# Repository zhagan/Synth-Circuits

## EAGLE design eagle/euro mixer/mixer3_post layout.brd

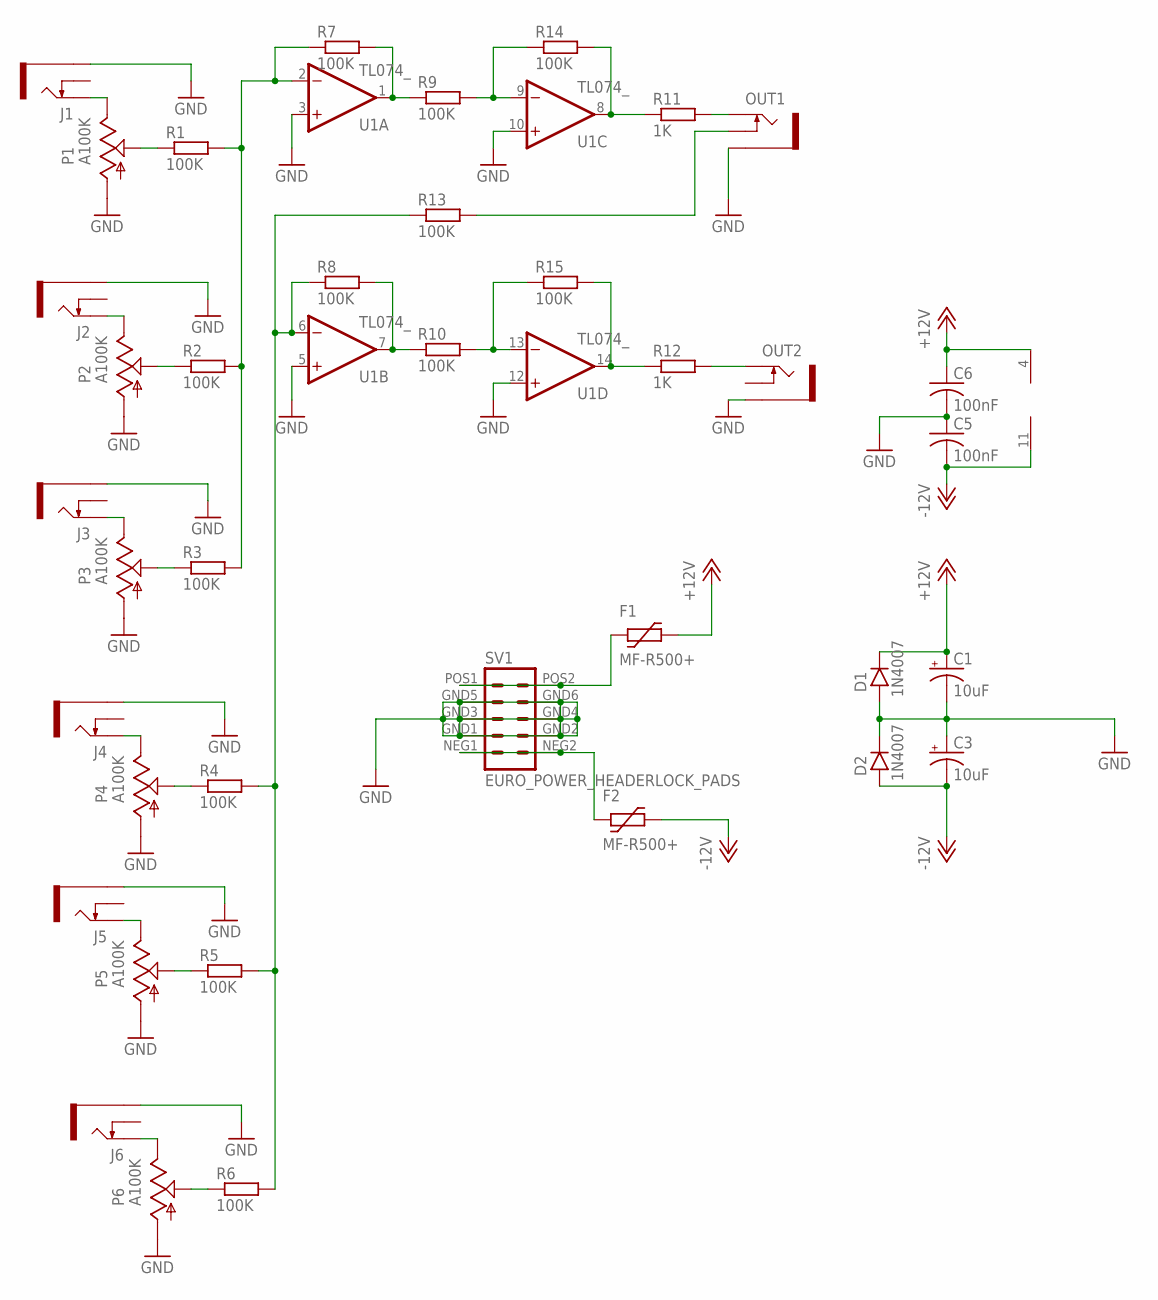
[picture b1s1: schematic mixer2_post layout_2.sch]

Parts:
C1, C3: 10uF; E2,5-7
C5, C6: 100nF; C075-032X103
D1, D2: 1N4007; DO41-3
F1, F2: MF-R500+; BOURNS-MF-R
J1, J2, J3, J4, J5, J6: THONKICONNNEW; WQP-PJ301M-12_JACK
OUT1, OUT2: THONKICONNNEW; WQP-PJ301M-12_JACK
P1, P2, P3, P4, P5, P6: A100K; 9MM_SNAP-IN_POT
R1, R2, R3, R4, R5, R6, R7, R8, R9, R10, R13, R14, R15: 100K; 7MM_RESISTOR
R11, R12: 1K; 7MM_RESISTOR
SV1: EURO_POWER_HEADERLOCK_PADS; EURO_PWR_HEADER_LOCK
U1: TL074_; DIL14

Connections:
+12V: C1.+, C6.1, D1.C, F1.P$2 (2), U1.4 (V+)
-12V: C3.-, C5.2, D2.A, F2.P$2 (2), U1.11 (V-)
GND: C1.-, C3.+, C5.1, C6.2, D1.A, D2.C, J1.P$3_SLEEVE (SLEEVE), J2.P$3_SLEEVE (SLEEVE), J3.P$3_SLEEVE (SLEEVE), J4.P$3_SLEEVE (SLEEVE), J5.P$3_SLEEVE (SLEEVE), J6.P$3_SLEEVE (SLEEVE), OUT1.P$3_SLEEVE (SLEEVE), OUT2.P$3_SLEEVE (SLEEVE), P1.1 (A), P2.1 (A), P3.1 (A), P4.1 (A), P5.1 (A), P6.1 (A), SV1.GND1 (4), SV1.GND2 (3), SV1.GND3 (6), SV1.GND4 (5), SV1.GND5 (8), SV1.GND6 (7), U1.3 (+IN), U1.5 (+IN), U1.10 (+IN), U1.12 (+IN)
unnamed: J2.P$1_TIP (TIP), P2.3 (E)
unnamed: P2.2 (S), R2.1
unnamed: J1.P$1_TIP (TIP), P1.3 (E)
unnamed: P1.2 (S), R1.1
unnamed: J3.P$1_TIP (TIP), P3.3 (E)
unnamed: P3.2 (S), R3.1
unnamed: J4.P$1_TIP (TIP), P4.3 (E)
unnamed: P4.2 (S), R4.1
unnamed: J5.P$1_TIP (TIP), P5.3 (E)
unnamed: P5.2 (S), R5.1
unnamed: J6.P$1_TIP (TIP), P6.3 (E)
unnamed: P6.2 (S), R6.1
unnamed: R1.2, R2.2, R3.2, R7.1, U1.2 (-IN)
unnamed: R8.2, R10.1, U1.7 (OUT)
unnamed: R9.2, R14.1, U1.9 (-IN)
unnamed: OUT1.P$1_TIP (TIP), R11.2
unnamed: R12.1, R15.2, U1.14 (OUT)
unnamed: R10.2, R15.1, U1.13 (-IN)
unnamed: R4.2, R5.2, R6.2, R8.1, R13.1, U1.6 (-IN)
unnamed: R11.1, R14.2, U1.8 (OUT)
unnamed: OUT1.P$2_SWITCH (SWITCH), R13.2
unnamed: OUT2.P$1_TIP (TIP), R12.2
unnamed: R7.2, R9.1, U1.1 (OUT)
unnamed: F2.P$1 (1), SV1.NEG1 (2), SV1.NEG2 (1)
unnamed: F1.P$1 (1), SV1.POS1 (10), SV1.POS2 (9)

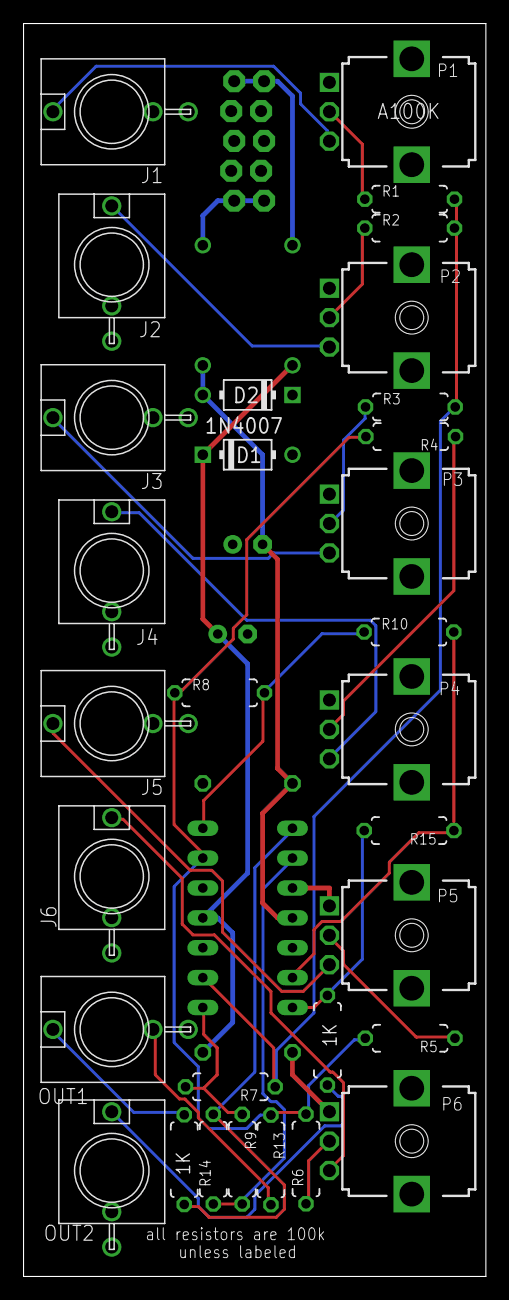
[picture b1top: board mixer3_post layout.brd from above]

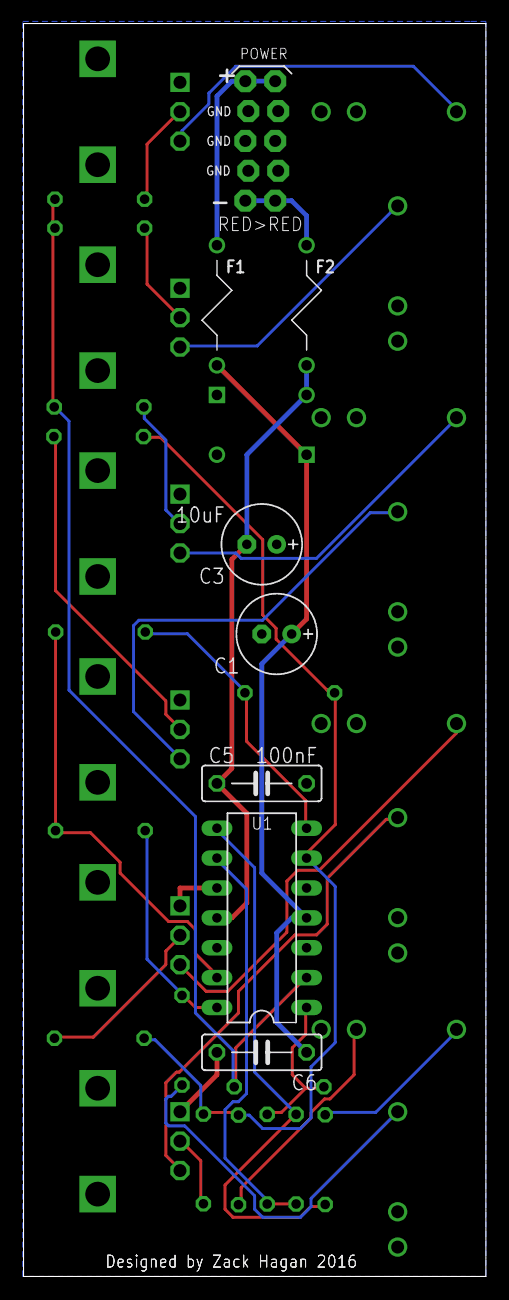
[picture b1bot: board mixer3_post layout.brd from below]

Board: 2 copper layers, 39.3 x 106.5 mm, 39 parts (8 on the bottom side), 28 nets.

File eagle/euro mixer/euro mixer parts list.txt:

Partlist

Exported from mixer3_post layout.sch at 4/12/17 4:11 PM

EAGLE Version 7.3.0 Copyright (c) 1988-2015 CadSoft

Assembly variant: 

Part     Value                      Device                     Package              Library           Sheet

C1       10uF                       CPOL-USE2.5-7              E2,5-7               resistor          1
C3       10uF                       CPOL-USE2.5-7              E2,5-7               resistor          1
C5       100nF                      C-US075-032X103            C075-032X103         resistor          1
C6       100nF                      C-US075-032X103            C075-032X103         resistor          1
D1       1N4007                     1N400X.3                   DO41-3               gm-diodes         1
D2       1N4007                     1N400X.3                   DO41-3               gm-diodes         1
F1       MF-R500+                   MF-R500+                   BOURNS-MF-R          ptc-littlefuse    1
F2       MF-R500+                   MF-R500+                   BOURNS-MF-R          ptc-littlefuse    1
J1       THONKICONNNEW              THONKICONNNEW              WQP-PJ301M-12_JACK   MusicThingModular 1
J2       THONKICONNNEW              THONKICONNNEW              WQP-PJ301M-12_JACK   MusicThingModular 1
J3       THONKICONNNEW              THONKICONNNEW              WQP-PJ301M-12_JACK   MusicThingModular 1
J4       THONKICONNNEW              THONKICONNNEW              WQP-PJ301M-12_JACK   MusicThingModular 1
J5       THONKICONNNEW              THONKICONNNEW              WQP-PJ301M-12_JACK   MusicThingModular 1
J6       THONKICONNNEW              THONKICONNNEW              WQP-PJ301M-12_JACK   MusicThingModular 1
OUT1     THONKICONNNEW              THONKICONNNEW              WQP-PJ301M-12_JACK   MusicThingModular 1
OUT2     THONKICONNNEW              THONKICONNNEW              WQP-PJ301M-12_JACK   MusicThingModular 1
P1       A100K                      9MM_SNAP-IN_POT_           9MM_SNAP-IN_POT      MusicThingModular 1
P2       A100K                      9MM_SNAP-IN_POT_           9MM_SNAP-IN_POT      MusicThingModular 1
P3       A100K                      9MM_SNAP-IN_POT_           9MM_SNAP-IN_POT      MusicThingModular 1
P4       A100K                      9MM_SNAP-IN_POT_           9MM_SNAP-IN_POT      MusicThingModular 1
P5       A100K                      9MM_SNAP-IN_POT_           9MM_SNAP-IN_POT      MusicThingModular 1
P6       A100K                      9MM_SNAP-IN_POT_           9MM_SNAP-IN_POT      MusicThingModular 1
R1       100K                       RESISTOR7MM                7MM_RESISTOR         MusicThingModular 1
R2       100K                       RESISTOR7MM                7MM_RESISTOR         MusicThingModular 1
R3       100K                       RESISTOR7MM                7MM_RESISTOR         MusicThingModular 1
R4       100K                       RESISTOR7MM                7MM_RESISTOR         MusicThingModular 1
R5       100K                       RESISTOR7MM                7MM_RESISTOR         MusicThingModular 1
R6       100K                       RESISTOR7MM                7MM_RESISTOR         MusicThingModular 1
R7       100K                       RESISTOR7MM                7MM_RESISTOR         MusicThingModular 1
R8       100K                       RESISTOR7MM                7MM_RESISTOR         MusicThingModular 1
R9       100K                       RESISTOR7MM                7MM_RESISTOR         MusicThingModular 1
R10      100K                       RESISTOR7MM                7MM_RESISTOR         MusicThingModular 1
R11      1K                         RESISTOR7MM                7MM_RESISTOR         MusicThingModular 1
R12      1K                         RESISTOR7MM                7MM_RESISTOR         MusicThingModular 1
R13      100K                       RESISTOR7MM                7MM_RESISTOR         MusicThingModular 1
R14      100K                       RESISTOR7MM                7MM_RESISTOR         MusicThingModular 1
R15      100K                       RESISTOR7MM                7MM_RESISTOR         MusicThingModular 1
SV1      EURO_POWER_HEADERLOCK_PADS EURO_POWER_HEADERLOCK_PADS EURO_PWR_HEADER_LOCK MusicThingModular 1
U1       TL074_                     TL074_                     DIL14                MusicThingModular 1

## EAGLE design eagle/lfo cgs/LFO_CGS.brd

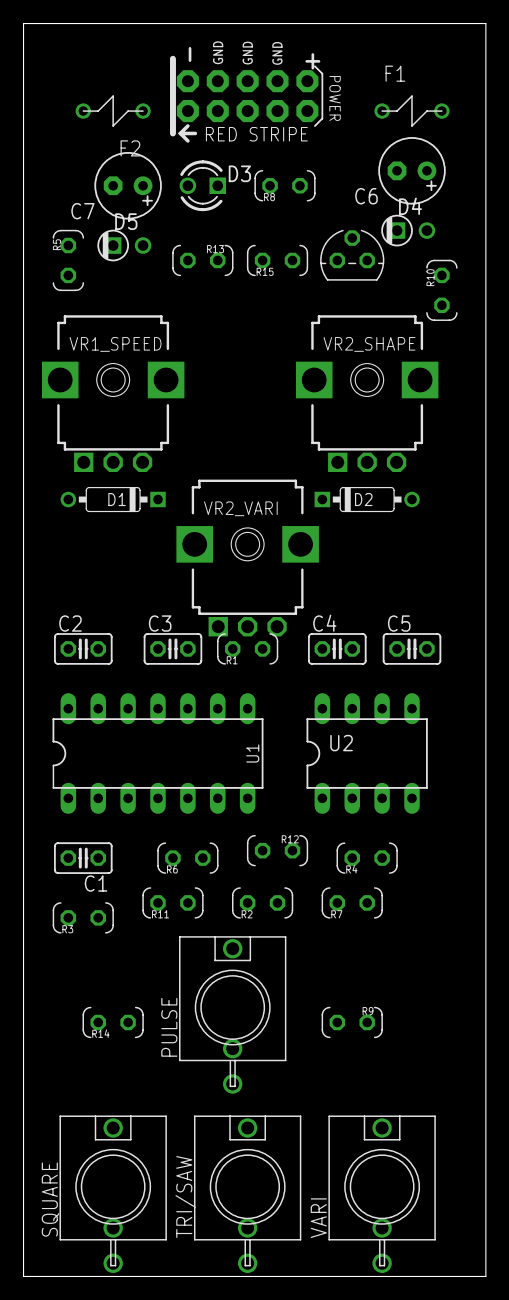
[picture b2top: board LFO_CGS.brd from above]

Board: 2 copper layers, 39.3 x 106.5 mm, 40 parts (0 on the bottom side), 26 nets, no tracks yet.

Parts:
C1: 47n; C025-025X050
C2, C3, C4, C5: 100n; C025-025X050
C6, C7: E2,5-6
D1, D2: 1N4148; DO35-7
D3: LED3MM
D4, D5: DO41-1
F1, F2: JK16-03-11
PULSE: THONKICONNNEW; WQP-PJ301M-12_JACK
R1: 150k; VERTICAL_RESISTOR
R2: 2k2; VERTICAL_RESISTOR
R3, R7, R8, R9, R13, R14, R15: 1k; VERTICAL_RESISTOR
R4, R10, R12: 100k; VERTICAL_RESISTOR
R5: 4k7; VERTICAL_RESISTOR
R6: 10k; VERTICAL_RESISTOR
R11: 47k; VERTICAL_RESISTOR
SQUARE: THONKICONNNEW; WQP-PJ301M-12_JACK
SV1: EURO_POWER_HEADERFAT_PADS; EURO_PWR_HEADER_FAT
T1: BC547; TO92
TRI/SAW: THONKICONNNEW; WQP-PJ301M-12_JACK
U1: TL074_; DIL14
U2: TL072_; DIL08
VARI: THONKICONNNEW; WQP-PJ301M-12_JACK
VR1_SPEED, VR2_VARI: B100k; 9MM_SNAP-IN_POT
VR2_SHAPE: B500k; 9MM_SNAP-IN_POT

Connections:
GND: C2.1, C3.2, C4.1, C5.2, C6.-, C7.+, D3.K, D4.C, D5.A, PULSE.P$3_SLEEVE, R3.1, R5.1, R8.1, R12.1, R15.1, SQUARE.P$3_SLEEVE, SV1.3, SV1.4, SV1.5, SV1.6, SV1.7, SV1.8, T1.3, TRI/SAW.P$3_SLEEVE, U1.3, U1.9, U1.12, VARI.P$3_SLEEVE
unnamed: R1.1, U1.10
unnamed: R1.2, R2.2, U1.8, VR1_SPEED.3
unnamed: PULSE.P$1_TIP, R2.1, R3.2
unnamed: R5.2, VR1_SPEED.1
unnamed: D1.A, D2.C, VR1_SPEED.2
unnamed: D1.C, VR2_SHAPE.1
unnamed: D2.A, VR2_SHAPE.3
unnamed: C1.1, R6.2, U1.2
unnamed: R6.1, VR2_SHAPE.2
unnamed: C1.2, R4.2, R7.2, R10.1, T1.2, U1.1, VR2_VARI.3
unnamed: R7.1, R8.2, TRI/SAW.P$1_TIP
unnamed: R11.1, U1.14
unnamed: R10.2, U1.13
unnamed: R11.2, R12.2, U1.5
unnamed: R14.2, U1.6, U1.7, VR2_VARI.1
unnamed: R14.1, R15.2, SQUARE.P$1_TIP
unnamed: D3.A, R13.2
unnamed: U2.3, VR2_VARI.2
unnamed: R9.2, U2.1, U2.2
unnamed: R9.1, VARI.P$1_TIP
unnamed: R13.1, T1.1
unnamed: F2.P$1, SV1.1
unnamed: F1.P$1, SV1.9
unnamed: C3.1, C5.1, C7.-, D5.C, F2.P$2, U1.11, U2.4
unnamed: C2.2, C4.2, C6.+, D4.A, F1.P$2, U1.4, U2.8
